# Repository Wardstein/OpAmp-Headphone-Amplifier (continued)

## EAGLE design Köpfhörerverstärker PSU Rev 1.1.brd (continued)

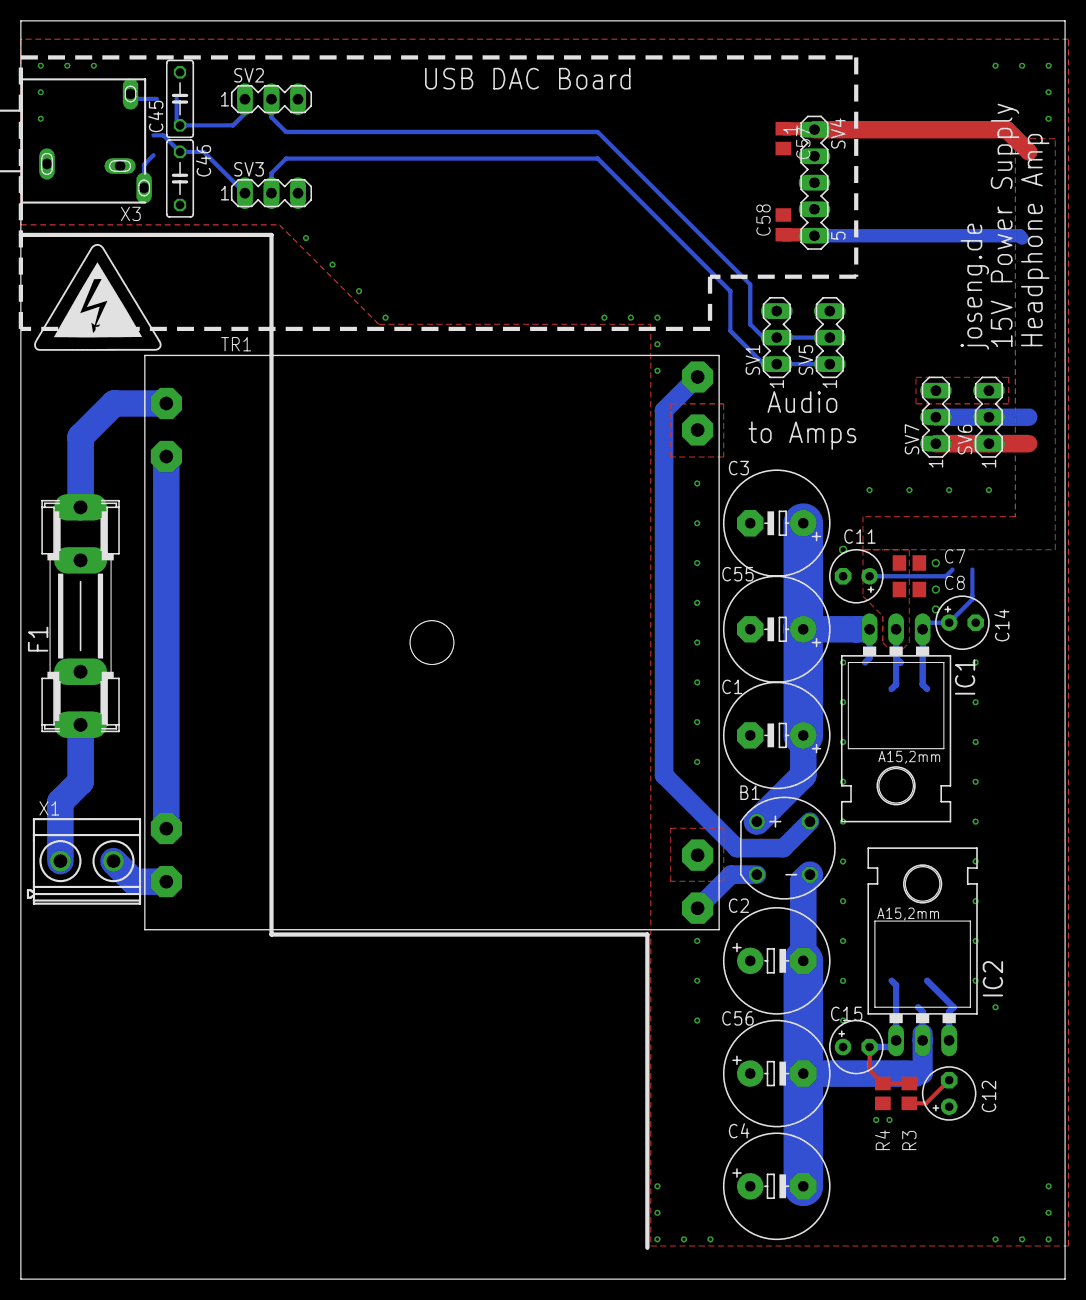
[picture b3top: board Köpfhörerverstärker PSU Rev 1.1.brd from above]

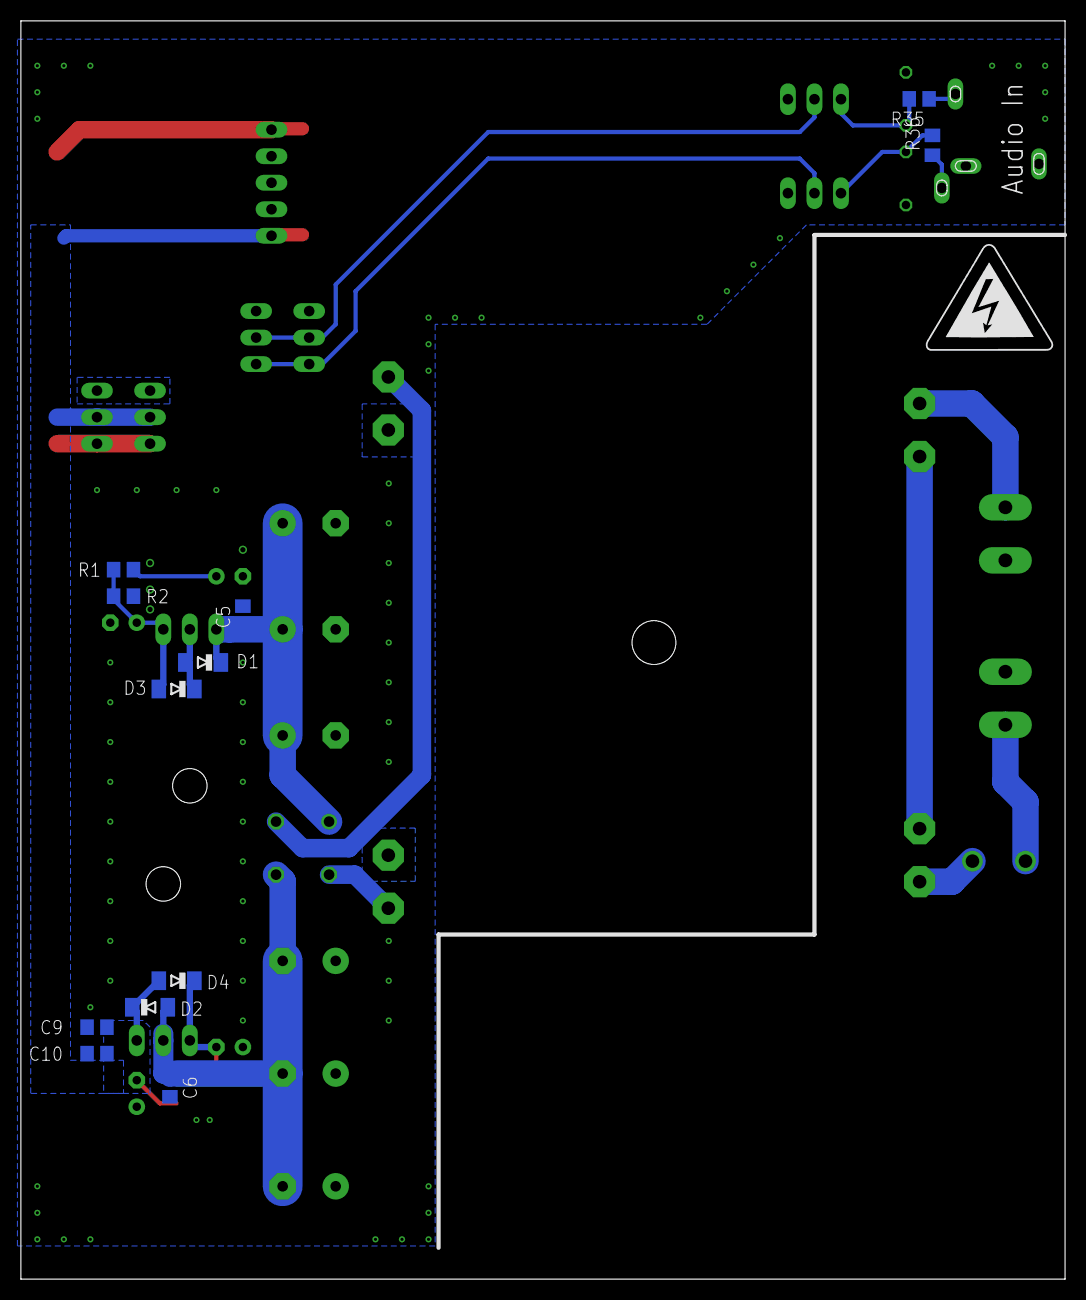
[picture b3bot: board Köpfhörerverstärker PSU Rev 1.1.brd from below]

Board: 2 copper layers, 100.0 x 120.5 mm, 46 parts (13 on the bottom side), 19 nets.

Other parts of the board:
U$1, U$2: HIGH_VOLTAGE_10MM

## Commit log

2023-01-20 Adding content
2023-01-20 Added gitignore file
2023-01-20 Added license
2023-01-20 Fixed readme
